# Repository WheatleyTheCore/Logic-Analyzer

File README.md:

# Logic-Analyzer
A Logic analyzer built around the MC9S08SH8 microprocessor.

The PCB was desgned with Kicad, and and firmware was written with Processor Expert.

An interrupt is triggered every time the signal line goes high, incrementing a counter. Each second this counter is read and reset, and the baud is calculated from that reading.

### TODO
Current version functions through use of interrupt pin, future version will use of a fast sample rate to handle higher baud rates better. A faster microprocessor will be required for this.

Future versions will also use the smallest bit in the received signal to calculate the baud, so almost any signal will be able to be used to calculate the baud rate(for example 00001000 or 11111110). This also ensures that the line being high or low for over one tick won't trip it up.

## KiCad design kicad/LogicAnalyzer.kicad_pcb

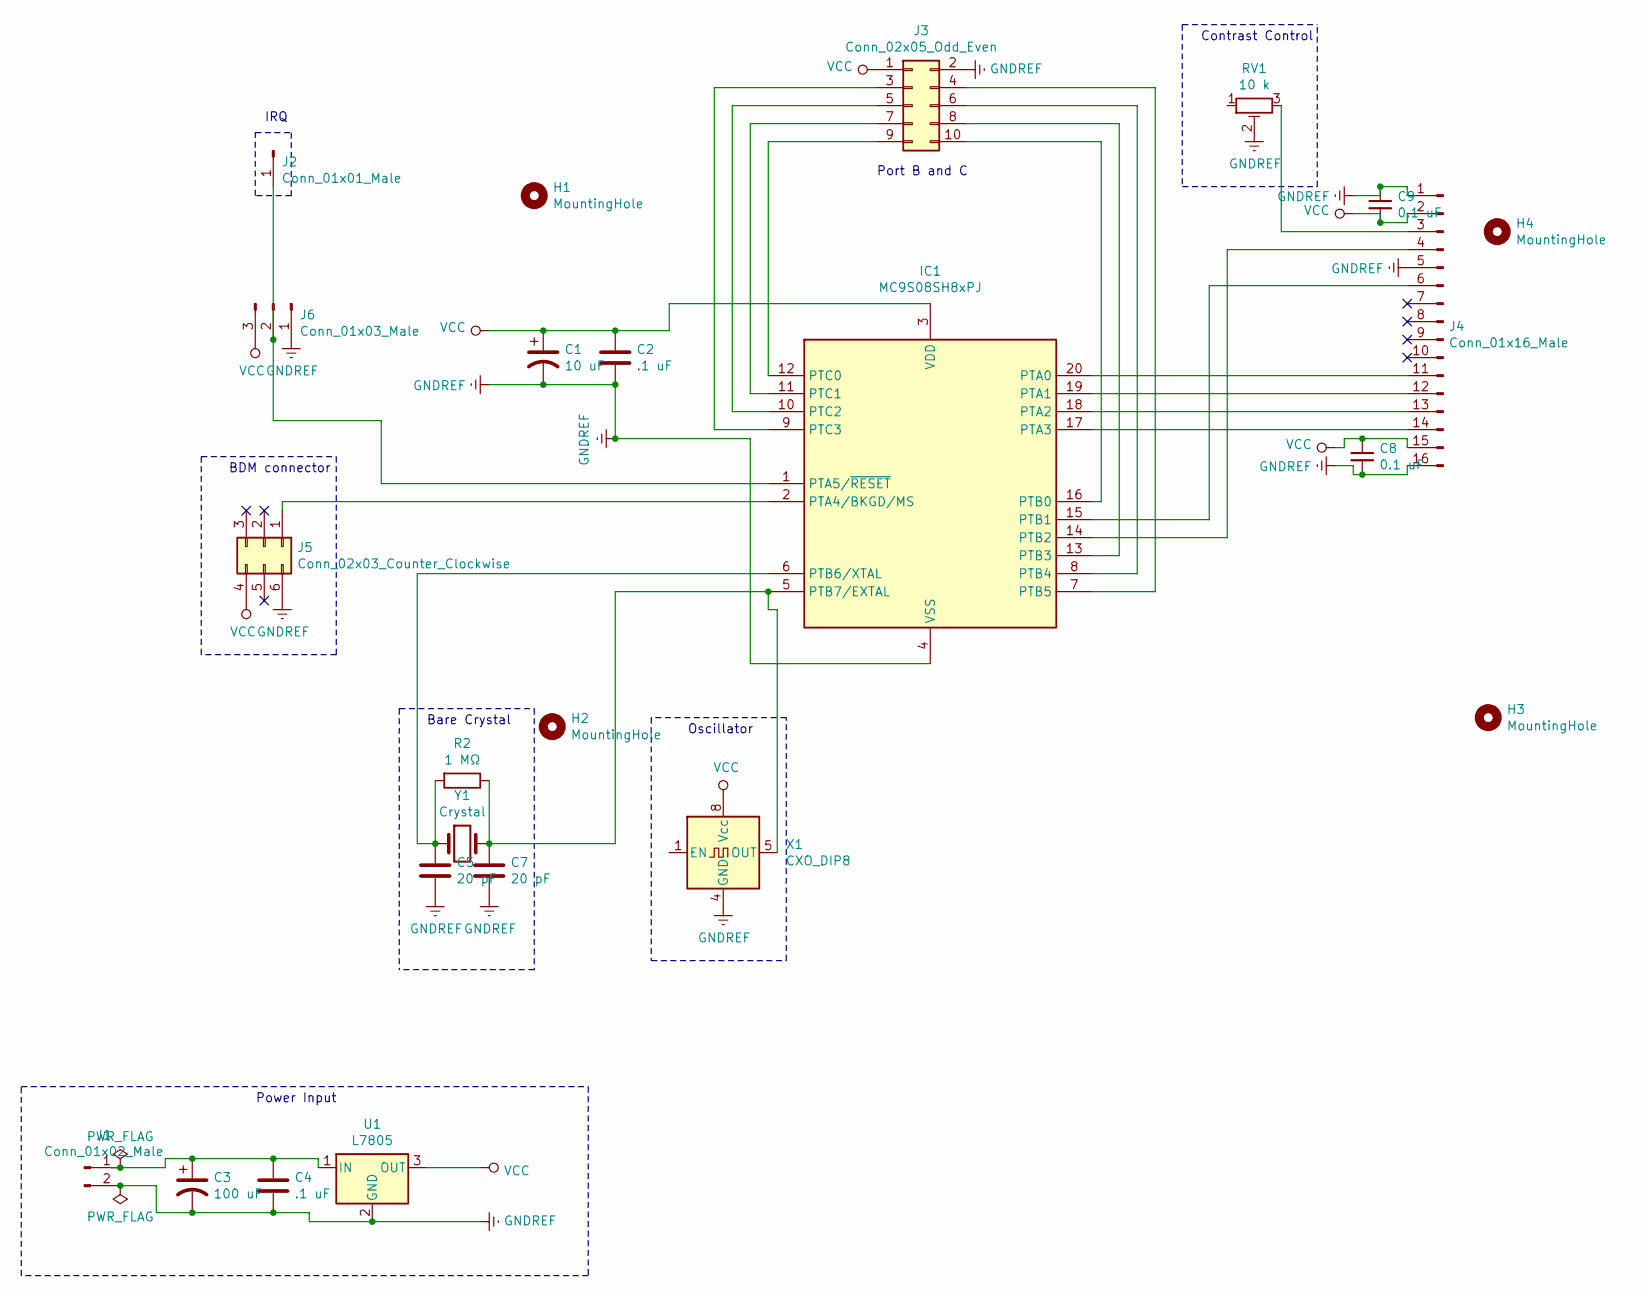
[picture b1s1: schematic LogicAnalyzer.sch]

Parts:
C1: 10 uF; CP_Radial_D8.0mm_P5.00mm
C2, C4: .1 uF; C_Disc_D7.0mm_W2.5mm_P5.00mm
C3: 100 uF; CP_Radial_D8.0mm_P5.00mm
C5, C7: 20 pF; C_Disc_D7.0mm_W2.5mm_P5.00mm
C8, C9: 0.1 uF; C_Disc_D7.0mm_W2.5mm_P5.00mm
H1, H2, H3, H4: MountingHole; MountingHole_3.5mm
IC1: MC9S08SH8xPJ; DIP-20_W7.62mm
J1: Conn_01x02_Male; PinHeader_1x02_P2.54mm_Vertical
J2: Conn_01x01_Male; PinHeader_1x01_P2.54mm_Vertical
J3: Conn_02x05_Odd_Even; IDC-Header_2x05_P2.54mm_Vertical
J4: Conn_01x16_Male; WC1602A
J5: Conn_02x03_Counter_Clockwise; IDC-Header_2x03_P2.54mm_Vertical
J6: Conn_01x03_Male; PinHeader_1x03_P2.54mm_Vertical
R2: 1 MΩ; R_Axial_DIN0207_L6.3mm_D2.5mm_P7.62mm_Horizontal
RV1: 10 k; Potentiometer_Bourns_3339P_Vertical
U1: L7805; TO-220-3_Vertical
X1: CXO_DIP8; Oscillator_DIP-8
Y1: Crystal; Crystal_HC49-4H_Vertical

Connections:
GNDREF: C1.2, C2.2, C3.2, C4.2, C5.2, C7.2, C8.2, C9.1, IC1.4 (VSS), J1.2, J3.2, J4.1, J4.5, J4.16, J5.6, J6.1, RV1.2, U1.2 (GND), X1.4 (GND)
unnamed: C3.1, C4.1, J1.1, U1.1 (IN)
unnamed: C5.1, IC1.6 (PTB6/XTAL), R2.2, Y1.1
unnamed: C7.1, IC1.5 (PTB7/EXTAL), R2.1, X1.5 (OUT), Y1.2
unnamed: IC1.1 (PTA5/~RESET), J2.1, J6.2
unnamed: IC1.2 (PTA4/BKGD/MS), J5.1
unnamed: IC1.7 (PTB5), J3.4
unnamed: IC1.8 (PTB4), J3.6
unnamed: IC1.9 (PTC3), J3.3
unnamed: IC1.10 (PTC2), J3.5
unnamed: IC1.11 (PTC1), J3.7
unnamed: IC1.12 (PTC0), J3.9
unnamed: IC1.13 (PTB3), J3.8
unnamed: IC1.14 (PTB2), J4.4
unnamed: IC1.15 (PTB1), J4.6
unnamed: IC1.16 (PTB0), J3.10
unnamed: IC1.17 (PTA3), J4.14
unnamed: IC1.18 (PTA2), J4.13
unnamed: IC1.19 (PTA1), J4.12
unnamed: IC1.20 (PTA0), J4.11
unnamed: J4.3, RV1.3
VCC: C1.1, C2.1, C8.1, C9.2, IC1.3 (VDD), J3.1, J4.2, J4.15, J5.4, J6.3, U1.3 (OUT), X1.8 (Vcc)

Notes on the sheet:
Power Input
Bare Crystal
Oscillator
Port B and C
Contrast Control
IRQ
BDM connector

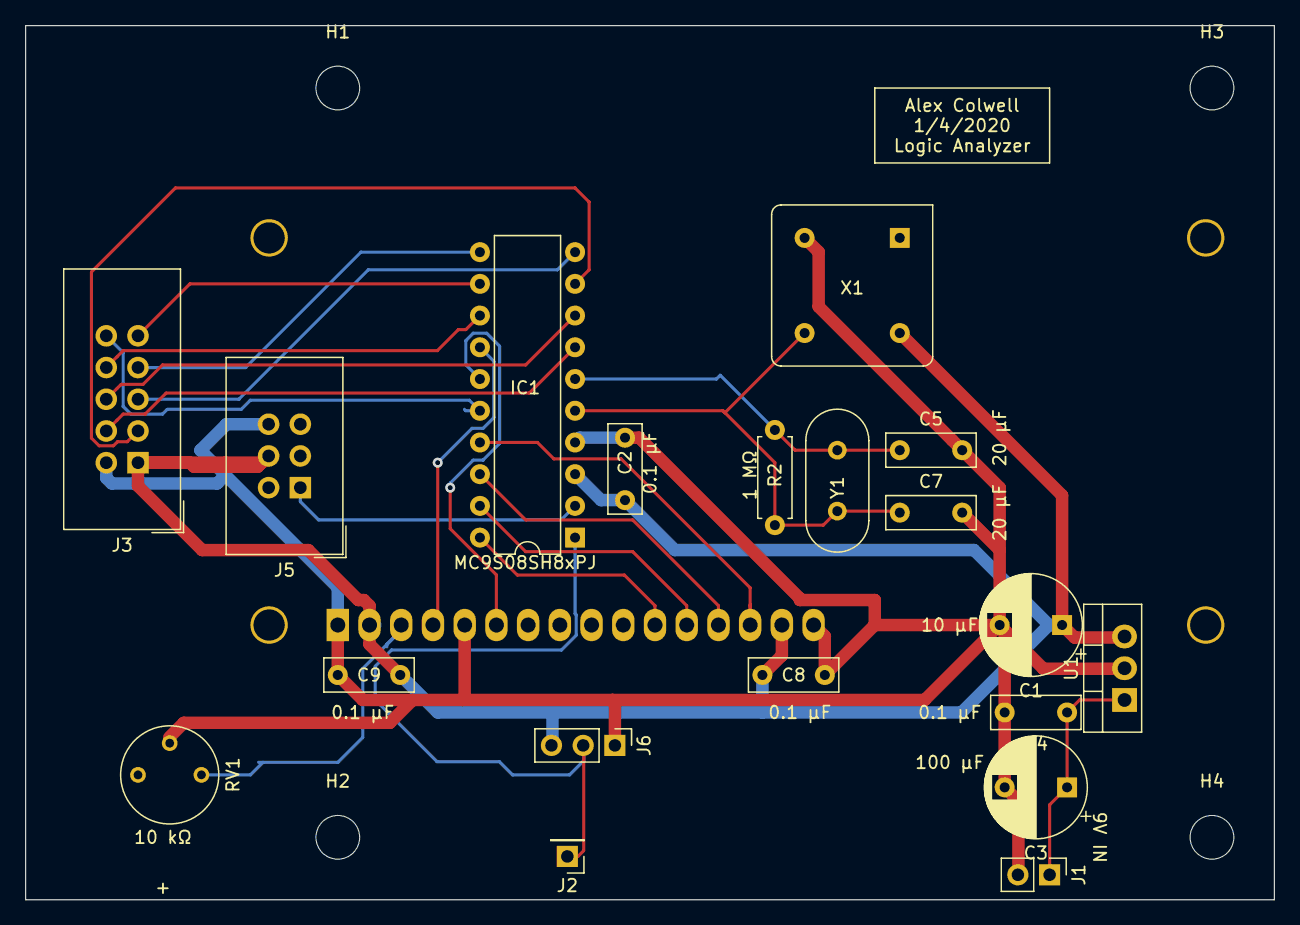
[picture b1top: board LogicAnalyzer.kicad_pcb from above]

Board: 2 copper layers, 100.0 x 70.0 mm, 24 parts (1 on the bottom side), 22 nets.

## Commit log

2020-01-14 added a folder
2020-01-14 fixed files
2020-01-31 Create eeschema
2020-01-31 Rename eeschema to eeschema.md
